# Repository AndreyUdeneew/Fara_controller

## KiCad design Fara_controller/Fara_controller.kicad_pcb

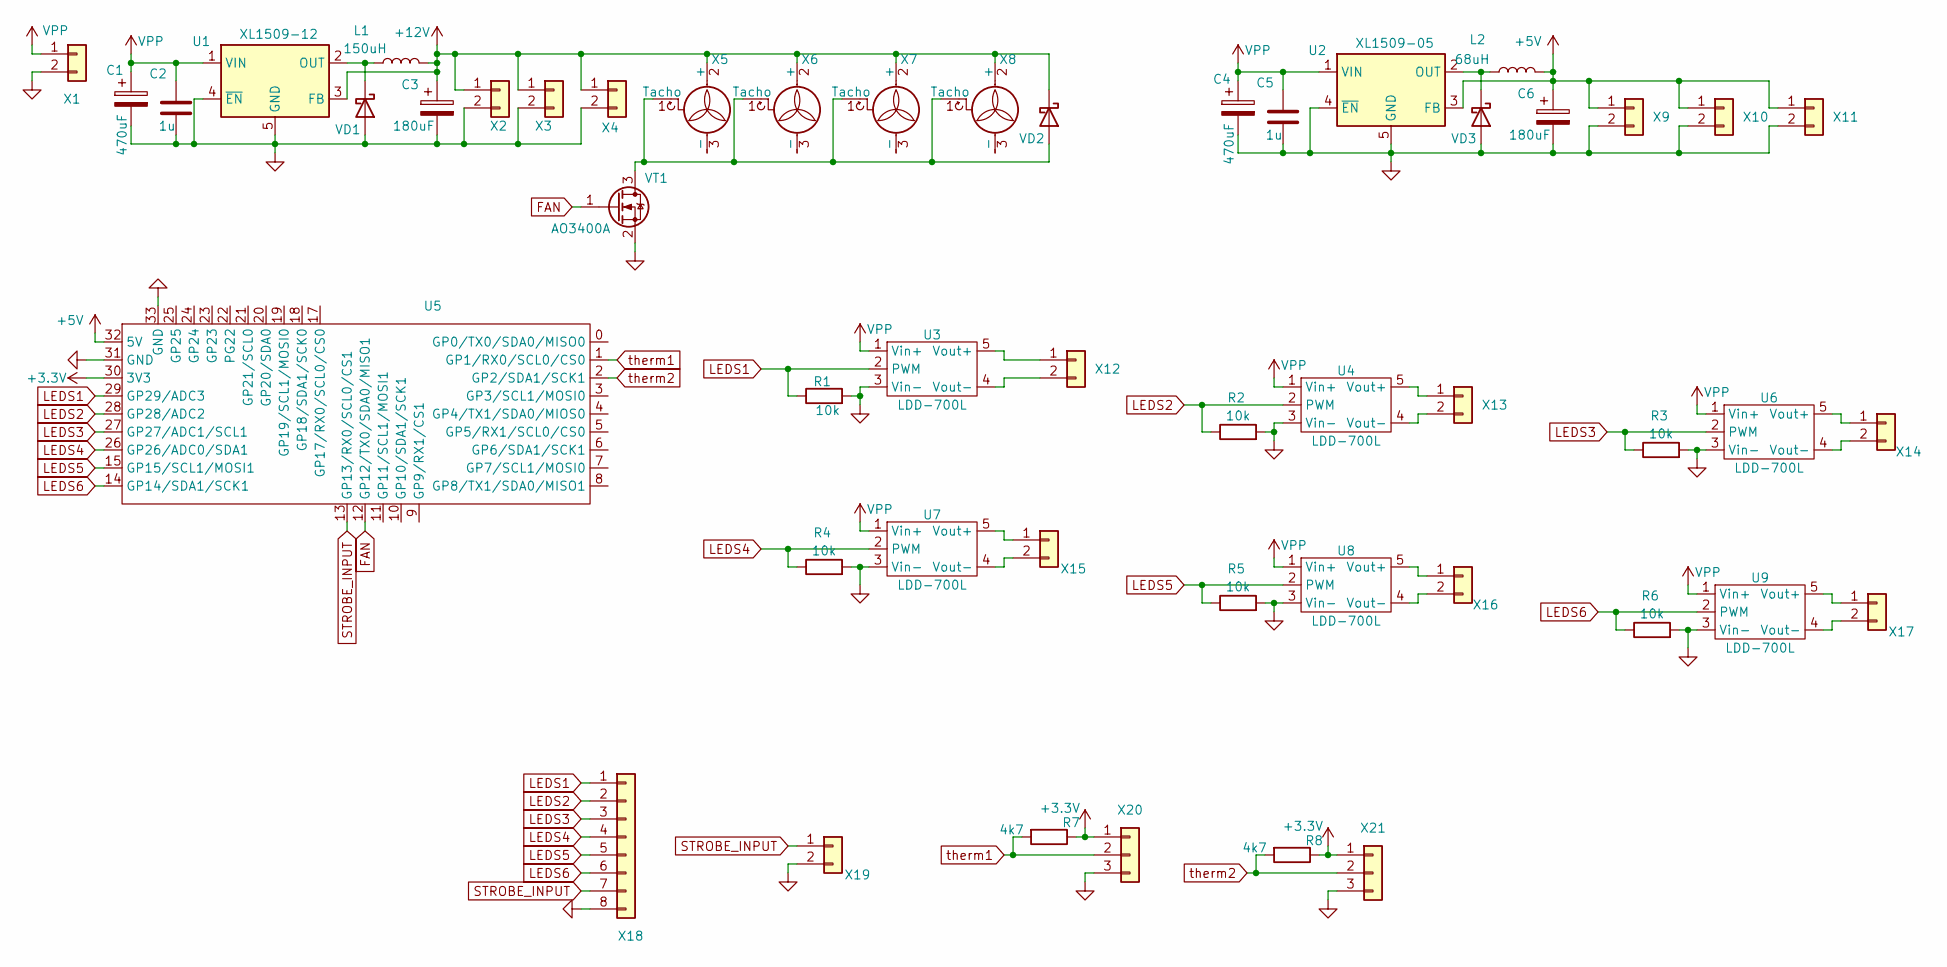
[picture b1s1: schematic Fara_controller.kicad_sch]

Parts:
C1, C4: 470uF; CP_Radial_D10.0mm_P5.00mm
C2, C5: 1u; C_0603_1608Metric_Pad1.08x0.95mm_HandSolder
C3, C6: 180uF; CP_Elec_6.3x7.7
L1: 150uH; L_TDK_VLS6045EX_VLS6045AF
L2: 68uH; L_Bourns_SRP1050WA
R1, R2, R3, R4, R5, R6: 10k; R_0603_1608Metric_Pad0.98x0.95mm_HandSolder
R7, R8: 4k7; R_0603_1608Metric_Pad0.98x0.95mm_HandSolder
U1: XL1509-12; SOIC-8-1EP_3.9x4.9mm_P1.27mm_EP2.95x4.9mm_Mask2.71x3.4mm_Th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
U2: XL1509-05; SOIC-8-1EP_3.9x4.9mm_P1.27mm_EP2.95x4.9mm_Mask2.71x3.4mm_Th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
U3, U4, U6, U7, U8, U9: LDD-700L
U5: RP2040Zero
VD1, VD2, VD3: CDBA3100-HF; D_SMA
VT1: AO3400A; SOT-23
X1: Conn_01x02; JST_VH_B2P-VH-B_1x02_P3.96mm_Vertical
X2, X3, X4, X9, X10, X11, X12, X13, X14, X15, X16, X17, X19: Conn_01x02; JST_XH_B2B-XH-A_1x02_P2.50mm_Vertical
X5, X6, X7, X8: Fan_3pin; FanPinHeader_1x03_P2.54mm_Vertical
X18: Objective; PinSocket_1x08_P1.27mm_Vertical
X20, X21: Conn_01x03; JST_XH_B3B-XH-A_1x03_P2.50mm_Vertical

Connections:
+3.3V: R7.1, R8.1, U5.30 (3V3), X20.1, X21.1
+5V: C6.1, L2.2, U2.3 (FB), U5.32 (5V), X9.1, X10.1, X11.1
+12V: C3.1, L1.2, U1.3 (FB), VD2.1 (K), X2.1, X3.1, X4.1, X5.2 (+), X6.2 (+), X7.2 (+), X8.2 (+)
FAN: U5.12 (GP12/TX0/SDA0/MISO1), VT1.1 (G)
GND: C1.2, C2.2, C3.2, C4.2, C5.2, C6.2, R1.2, R2.2, R3.2, R4.2, R5.2, R6.2, U1.4 (~EN), U1.5 (GND), U1.6 (GND), U1.7 (GND), U1.8 (GND), U1.9 (GND), U2.4 (~EN), U2.5 (GND), U2.6 (GND), U2.7 (GND), U2.8 (GND), U2.9 (GND), U3.3 (Vin-), U4.3 (Vin-), U5.31 (GND), U5.33 (GND), U6.3 (Vin-), U7.3 (Vin-), U8.3 (Vin-), U9.3 (Vin-), VD1.2 (A), VD3.2 (A), VT1.2 (S), X1.2, X2.2, X3.2, X4.2, X9.2, X10.2, X11.2, X18.8, X19.2, X20.3, X21.3
LEDS1: R1.1, U3.2 (PWM), U5.29 (GP29/ADC3), X18.1
LEDS2: R2.1, U4.2 (PWM), U5.28 (GP28/ADC2), X18.2
LEDS3: R3.1, U5.27 (GP27/ADC1/SCL1), U6.2 (PWM), X18.3
LEDS4: R4.1, U5.26 (GP26/ADC0/SDA1), U7.2 (PWM), X18.4
LEDS5: R5.1, U5.15 (GP15/SCL1/MOSI1), U8.2 (PWM), X18.5
LEDS6: R6.1, U5.14 (GP14/SDA1/SCK1), U9.2 (PWM), X18.6
unnamed: L1.1, U1.2 (OUT), VD1.1 (K)
unnamed: L2.1, U2.2 (OUT), VD3.1 (K)
unnamed: U3.5 (Vout+), X12.1
unnamed: U3.4 (Vout-), X12.2
unnamed: U4.5 (Vout+), X13.1
unnamed: U4.4 (Vout-), X13.2
unnamed: U6.5 (Vout+), X14.1
unnamed: U6.4 (Vout-), X14.2
unnamed: U7.5 (Vout+), X15.1
unnamed: U7.4 (Vout-), X15.2
unnamed: U8.5 (Vout+), X16.1
unnamed: U8.4 (Vout-), X16.2
unnamed: U9.5 (Vout+), X17.1
unnamed: U9.4 (Vout-), X17.2
unnamed: VD2.2 (A), VT1.3 (D), X5.1 (Tacho), X6.1 (Tacho), X7.1 (Tacho), X8.1 (Tacho)
STROBE_INPUT: U5.13 (GP13/RX0/SCL0/CS1), X18.7, X19.1
VPP: C1.1, C2.1, C4.1, C5.1, U1.1 (VIN), U2.1 (VIN), U3.1 (Vin+), U4.1 (Vin+), U6.1 (Vin+), U7.1 (Vin+), U8.1 (Vin+), U9.1 (Vin+), X1.1
therm1: R7.2, U5.1 (GP1/RX0/SCL0/CS0), X20.2
therm2: R8.2, U5.2 (GP2/SDA1/SCK1), X21.2

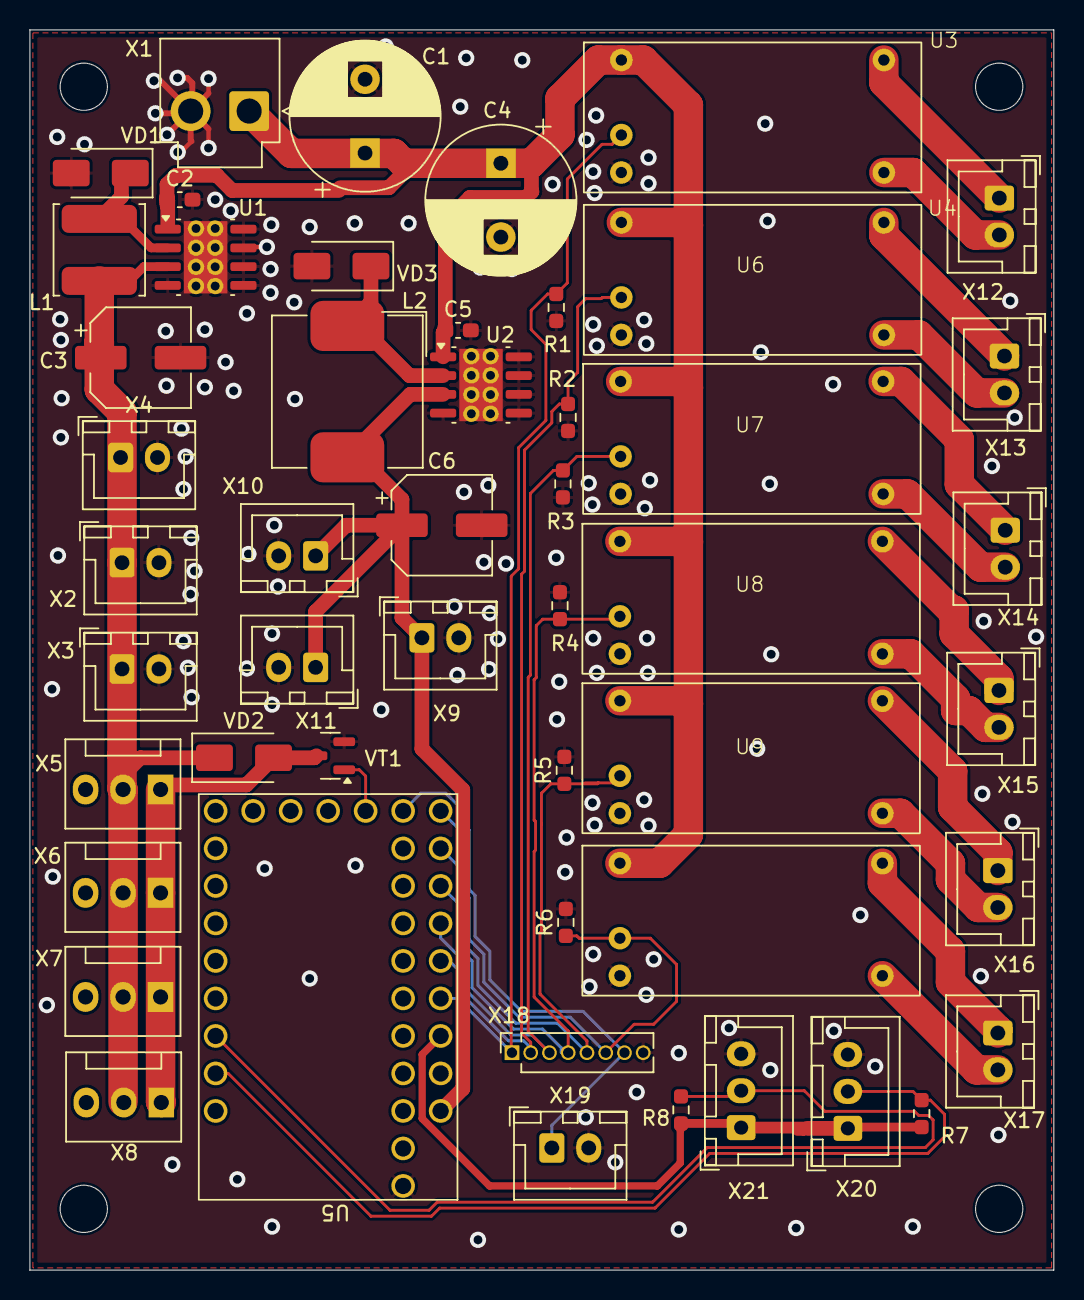
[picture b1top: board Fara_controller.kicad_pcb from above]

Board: 2 copper layers, 69.3 x 84.0 mm, 50 parts (0 on the bottom side), 30 nets.

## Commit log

2024-12-12 v0.1 draft routing was created
2024-12-27 v0.2 draft routing of the 24V edition
2024-12-28 v0.3 Seems 2B ready
